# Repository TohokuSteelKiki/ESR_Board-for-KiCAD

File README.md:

# ESR_Board-for-KiCAD
(ヨウ)ESR用のボード D-0363をKiCADで書き直したデータ

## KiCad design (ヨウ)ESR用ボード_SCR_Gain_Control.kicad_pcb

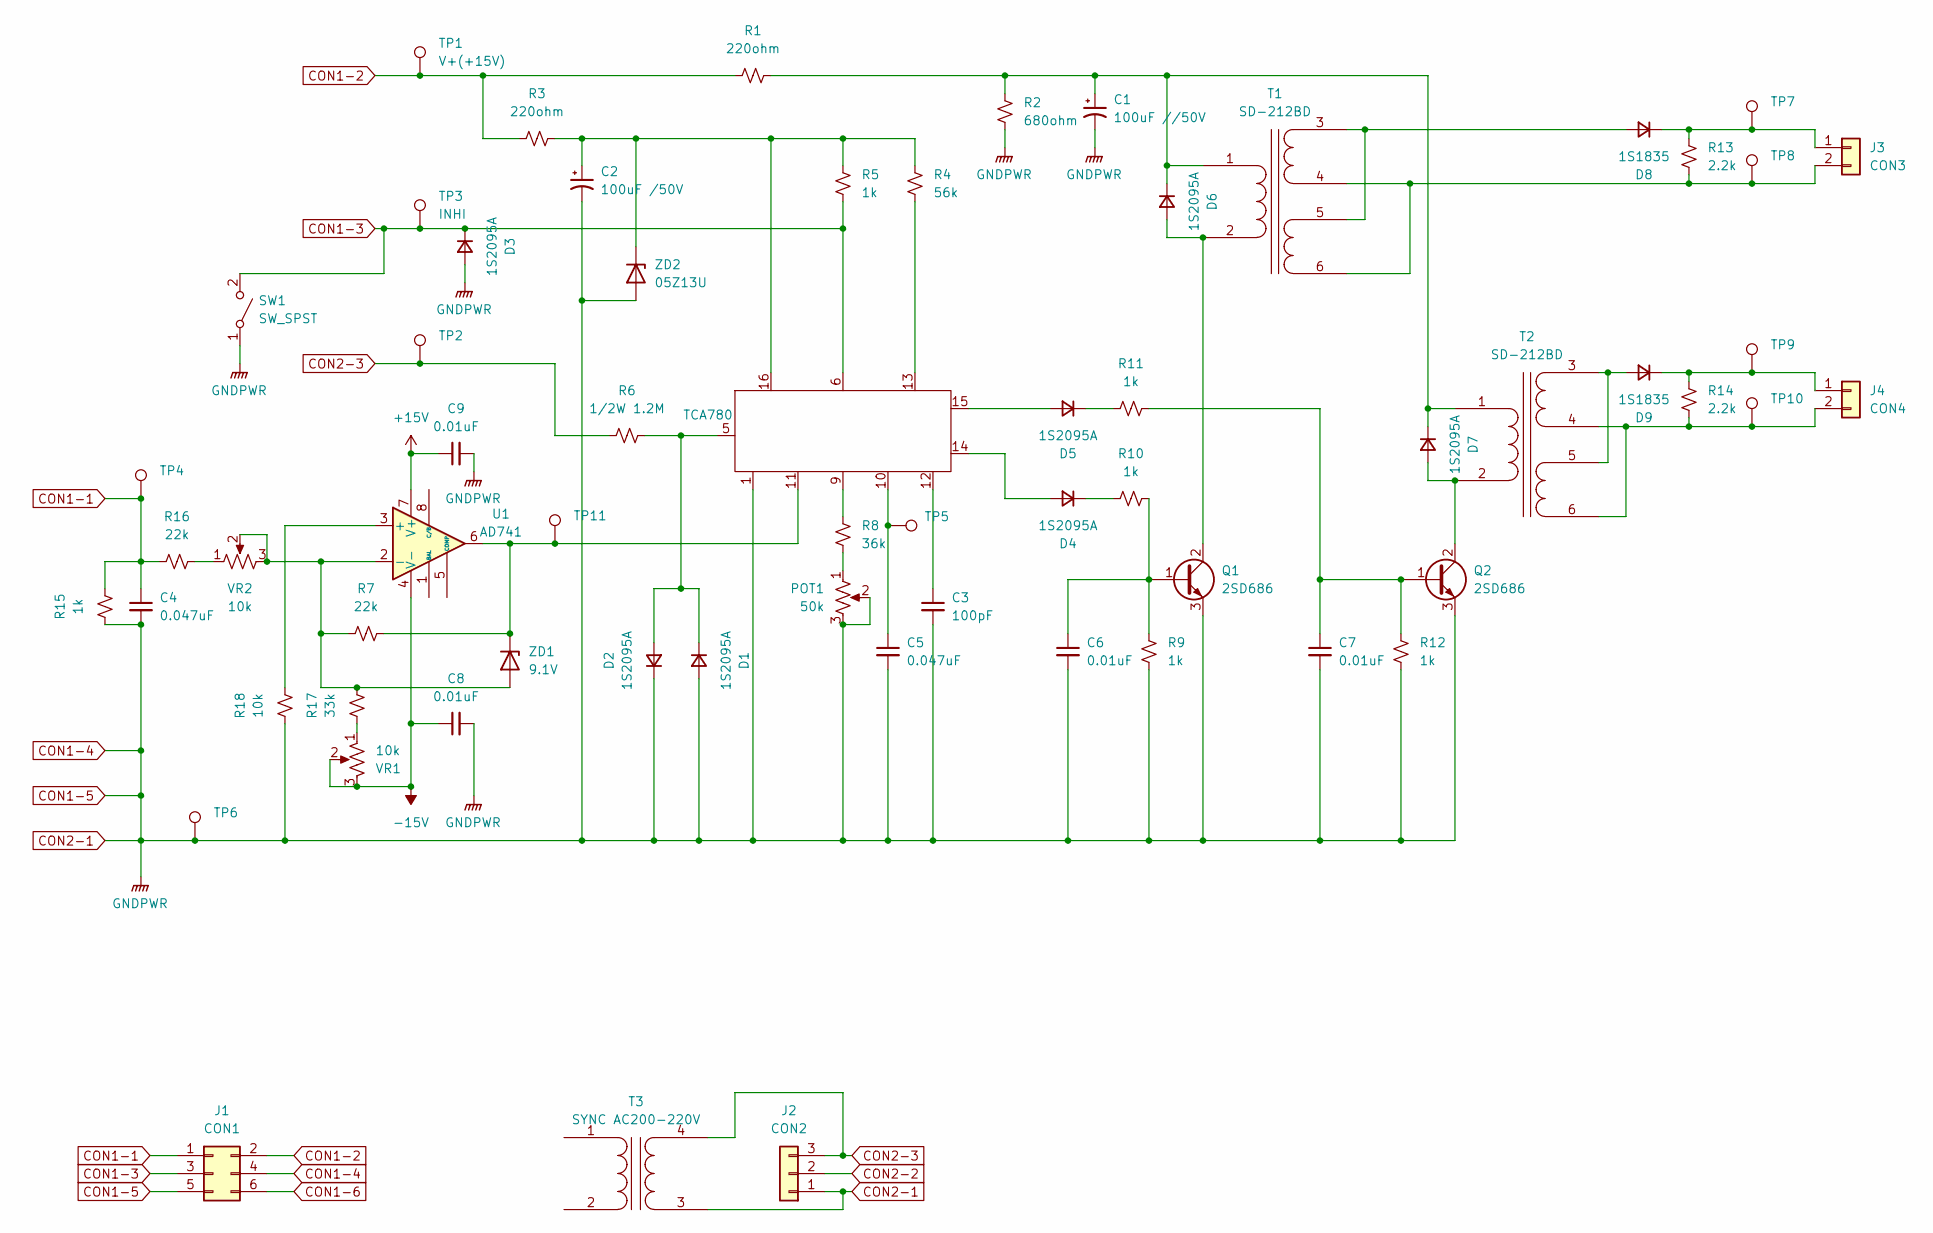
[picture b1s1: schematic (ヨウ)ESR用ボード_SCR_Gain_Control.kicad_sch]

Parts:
C1: 100uF //50V; CP_Radial_D8.0mm_P3.50mm
C2: 100uF /50V; CP_Radial_D8.0mm_P3.50mm
C3: 100pF; C_Disc_D5.0mm_W2.5mm_P5.00mm
C4, C5: 0.047uF; C_Disc_D5.0mm_W2.5mm_P5.00mm
C6, C7, C8, C9: 0.01uF; C_Disc_D5.0mm_W2.5mm_P5.00mm
D1, D2, D3, D4, D5, D6, D7: 1S2095A; D_A-405_P10.16mm_Horizontal
D8, D9: 1S1835; D_A-405_P10.16mm_Horizontal
J1: CON1; B06P-VL
J2: CON2; B03P-VL
J3: CON3; JST_NV_B02P-NV_1x02_P5.00mm_Vertical
J4: CON4; JST_NV_B02P-NV_1x02_P5.00mm_Vertical
POT1: 50k; Potentiometer_Bourns_3296W_Vertical
Q1, Q2: 2SD686; TO-220-3_Horizontal_TabDown
R1, R3: 220ohm; R_Axial_DIN0207_L6.3mm_D2.5mm_P10.16mm_Horizontal
R2: 680ohm; R_Axial_DIN0207_L6.3mm_D2.5mm_P10.16mm_Horizontal
R4: 56k; R_Axial_DIN0207_L6.3mm_D2.5mm_P10.16mm_Horizontal
R5, R9, R10, R11, R12, R15: 1k; R_Axial_DIN0207_L6.3mm_D2.5mm_P10.16mm_Horizontal
R6: 1/2W 1.2M; R_Axial_DIN0207_L6.3mm_D2.5mm_P15.24mm_Horizontal
R7, R16: 22k; R_Axial_DIN0207_L6.3mm_D2.5mm_P10.16mm_Horizontal
R8: 36k; R_Axial_DIN0207_L6.3mm_D2.5mm_P10.16mm_Horizontal
R13, R14: 2.2k; R_Axial_DIN0207_L6.3mm_D2.5mm_P10.16mm_Horizontal
R17: 33k; R_Axial_DIN0207_L6.3mm_D2.5mm_P10.16mm_Horizontal
R18: 10k; R_Axial_DIN0207_L6.3mm_D2.5mm_P10.16mm_Horizontal
SW1: SW_SPST
T1, T2: SD-212BD; Transformer_Myrra_EI30-5_44000_Horizontal
T3: SYNC AC200-220V
TCA780: DIP-16_W7.62mm
TP1: V+(+15V); TestPoint_Loop_D2.54mm_Drill1.5mm_Beaded
TP2, TP4, TP5, TP6, TP7, TP8, TP9, TP10, TP11: TestPoint_Loop_D2.54mm_Drill1.5mm_Beaded
TP3: INHI; TestPoint_Loop_D2.54mm_Drill1.5mm_Beaded
U1: AD741; TO-5-8
VR1, VR2: 10k; Potentiometer_Bourns_3296W_Vertical
ZD1: 9.1V; D_A-405_P10.16mm_Horizontal
ZD2: 05Z13U; D_A-405_P10.16mm_Horizontal

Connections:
+15V: C9.1, U1.7 (V+)
-15V: C8.1, U1.4 (V-), VR1.2, VR1.3
CON1-1: C4.1, J1.1, R15.2, R16.1, TP4.1
CON1-2: J1.2, R1.1, R3.1, TP1.1
CON1-3: D3.1 (K), J1.3, R5.1, SW1.2 (B), TCA780.6, TP3.1
CON1-4: C1.2, C2.2, C3.2, C4.2, C5.2, C6.2, C7.2, C8.2, C9.2, D1.2 (A), D2.1 (K), D3.2 (A), J1.4, J1.5, J2.1, POT1.2, POT1.3, Q1.3 (E), Q2.3 (E), R2.1, R9.1, R12.1, R15.1, R18.1, SW1.1 (A), T3.3 (SA), TCA780.1, TP6.1, ZD2.2 (A)
CON1-6: J1.6
CON2-2: J2.2
CON2-3: J2.3, R6.1, T3.4 (SB), TP2.1
unnamed: C3.1, TCA780.12
unnamed: C5.1, TCA780.10, TP5.1
unnamed: D1.1 (K), D2.2 (A), R6.2, TCA780.5
unnamed: D4.2 (A), TCA780.14
unnamed: D4.1 (K), R10.2
unnamed: D5.2 (A), TCA780.15
unnamed: D5.1 (K), R11.2
unnamed: D6.2 (A), Q1.2 (C), T1.2 (AB)
unnamed: C1.1, D6.1 (K), D7.1 (K), R1.2, R2.2, T1.1 (AA), T2.1 (AA)
unnamed: D7.2 (A), Q2.2 (C), T2.2 (AB)
unnamed: D8.2 (A), T1.3 (SA), T1.5 (SC)
unnamed: D8.1 (K), J3.1, R13.2, TP7.1
unnamed: D9.2 (A), T2.3 (SA), T2.5 (SC)
unnamed: D9.1 (K), J4.1, R14.2, TP9.1
unnamed: J3.2, R13.1, T1.4 (SB), T1.6 (SD), TP8.1
unnamed: J4.2, R14.1, T2.4 (SB), T2.6 (SD), TP10.1
unnamed: POT1.1, R8.2
unnamed: C6.1, Q1.1 (B), R9.2, R10.1
unnamed: C7.1, Q2.1 (B), R11.1, R12.2
unnamed: R4.1, TCA780.13
unnamed: R8.1, TCA780.9
unnamed: R16.2, VR2.1
unnamed: R17.1, VR1.1
unnamed: R18.2, U1.3 (+)
unnamed: R7.1, R17.2, U1.2 (-), VR2.2, VR2.3, ZD1.2 (A)
unnamed: R7.2, TCA780.11, TP11.1, U1.6, ZD1.1 (K)
unnamed: C2.1, R3.2, R4.2, R5.2, TCA780.16, ZD2.1 (K)

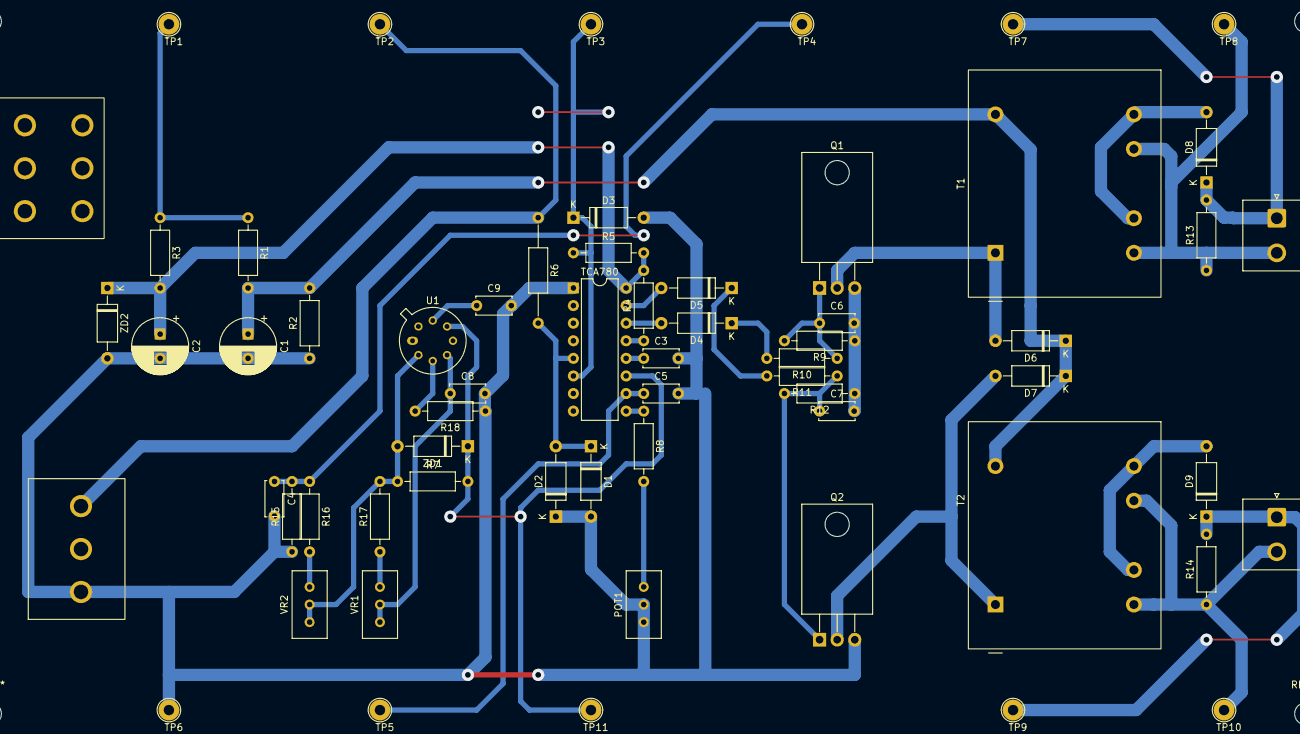
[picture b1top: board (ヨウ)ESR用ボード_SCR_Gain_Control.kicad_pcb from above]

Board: 2 copper layers, 62 parts (0 on the bottom side), 34 nets.

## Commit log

2025-02-07 .gitignore
